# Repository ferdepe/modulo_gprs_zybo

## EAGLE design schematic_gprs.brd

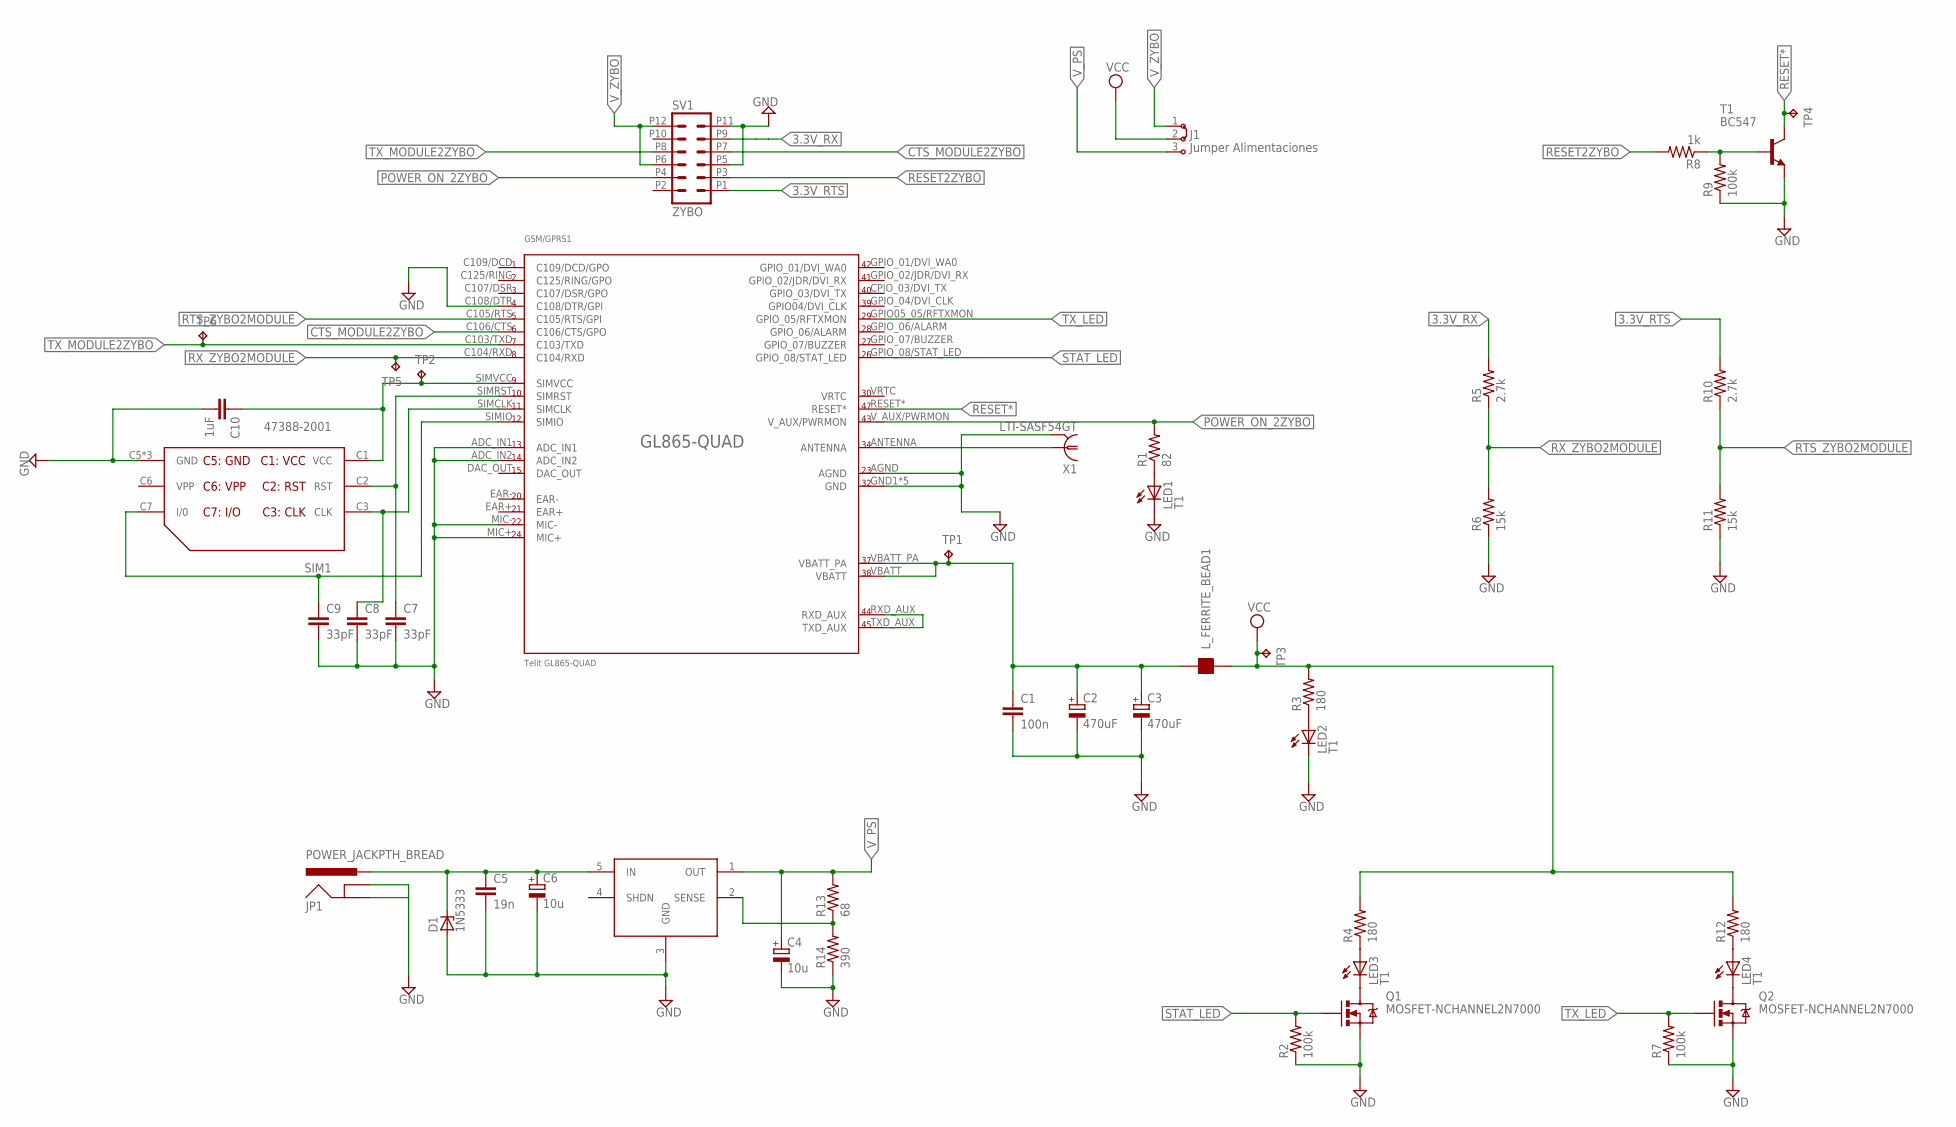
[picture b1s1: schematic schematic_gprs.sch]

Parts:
C1: 100n; C2.5-2
C2, C3: 470uF; E3,5-8
C4: 10u; E2-5
C5: 19n; C050-025X075
C6: 10u; E1,8-4
C7, C8, C9: 33pF; C025-024X044
C10: 1uF; CAP-PTH-SMALL-KIT
D1: 1N5333; C1702-15
GSM/GPRS1: Telit GL865-QUAD; GL865-QUAD
J1: Jumper Alimentaciones; 04C
JP1: POWER_JACKPTH_BREAD; POWER_JACK_PTH_BREAD
LED1, LED2, LED3, LED4: T1; LED3MM
L_FERRITE_BEAD1: FERRITEBEAD2; 0207/7
Q1, Q2: MOSFET-NCHANNEL2N7000; TO-92
R1: 82; 0207/7
R2, R7, R9: 100k; 0207/7
R3, R4, R12: 180; 0207/7
R5, R10: 2.7k; 0207/7
R6, R11: 15k; 0207/7
R8: 1k; 0207/7
R13: 68; 0207/7
R14: 390; 0207/7
SIM1: 47388-2001
SV1: ZYBO; MA06-2
T1: BC547; TO92
TP1, TP2, TP3, TP4, TP5, TP6: TPPAD1-13; P1-13
U$1: LT1528; Q5-DD
X1: LTI-SASF54GT

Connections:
3.3V_RTS: R10.2, SV1.P1 (1)
3.3V_RX: R5.2, SV1.P9 (9)
CTS_MODULE2ZYBO: GSM/GPRS1.C106/CTS (C106/CTS/GPO), SV1.P7 (7)
GND: C1.2, C2.-, C3.-, C4.-, C5.2, C6.-, C7.2, C8.2, C9.2, C10.2, D1.A, GSM/GPRS1.ADC_IN1, GSM/GPRS1.ADC_IN2, GSM/GPRS1.AGND, GSM/GPRS1.C108/DTR (C108/DTR/GPI), GSM/GPRS1.GND1 (GND), GSM/GPRS1.GND2 (GND), GSM/GPRS1.GND3 (GND), GSM/GPRS1.GND4 (GND), GSM/GPRS1.GND5 (GND), GSM/GPRS1.MIC+, GSM/GPRS1.MIC-, JP1.GND, JP1.GNDBREAK, LED1.K (C), LED2.K (C), Q1.1 (S), Q2.1 (S), R2.1, R6.1, R7.1, R9.1, R11.1, R14.1, SIM1.C5 (GND), SIM1.GND1 (GND), SIM1.GND2 (GND), SV1.P5 (5), SV1.P11 (11), T1.1 (E), U$1.3 (GND), X1.2, X1.3 (2), X1.4 (2), X1.5 (2)
unnamed: GSM/GPRS1.ANTENNA, X1.1
unnamed: C10.1, GSM/GPRS1.SIMVCC, SIM1.C1 (VCC), TP2.TP
unnamed: LED4.A, R12.1
unnamed: C7.1, GSM/GPRS1.SIMRST, SIM1.C2 (RST)
unnamed: C8.1, GSM/GPRS1.SIMCLK, SIM1.C3 (CLK)
unnamed: C9.1, GSM/GPRS1.SIMIO, SIM1.C7 (I/0)
unnamed: R8.1, R9.2, T1.2 (B)
unnamed: LED1.A, R1.1
unnamed: LED4.K (C), Q2.3 (D)
unnamed: C1.1, C2.+, C3.+, GSM/GPRS1.VBATT, GSM/GPRS1.VBATT_PA, L_FERRITE_BEAD1.1 (A), TP1.TP
unnamed: C5.1, C6.+, D1.C, JP1.PWR, U$1.5 (IN)
unnamed: LED3.A, R4.1
unnamed: LED3.K (C), Q1.3 (D)
unnamed: R13.1, R14.2, U$1.2 (SENSE)
unnamed: LED2.A, R3.1
unnamed: GSM/GPRS1.RXD_AUX, GSM/GPRS1.TXD_AUX
POWER_ON_2ZYBO: GSM/GPRS1.V_AUX/PWRMON, R1.2, SV1.P4 (4)
RESET2ZYBO: R8.2, SV1.P3 (3)
RESET*: GSM/GPRS1.RESET*, T1.3 (C), TP4.TP
RTS_ZYBO2MODULE: GSM/GPRS1.C105/RTS (C105/RTS/GPI), R10.1, R11.2
RX_ZYBO2MODULE: GSM/GPRS1.C104/RXD, R5.1, R6.2, TP5.TP
STAT_LED: GSM/GPRS1.GPIO_08/STAT_LED, Q1.2 (G), R2.2
TX_LED: GSM/GPRS1.GPIO05_05/RFTXMON (GPIO_05/RFTXMON), Q2.2 (G), R7.2
TX_MODULE2ZYBO: GSM/GPRS1.C103/TXD, SV1.P8 (8), TP6.TP
VCC: J1.2, L_FERRITE_BEAD1.2 (B), R3.2, R4.2, R12.2, TP3.TP
V_PS: C4.+, J1.3, R13.2, U$1.1 (OUT)
V_ZYBO: J1.1, SV1.P6 (6), SV1.P12 (12)

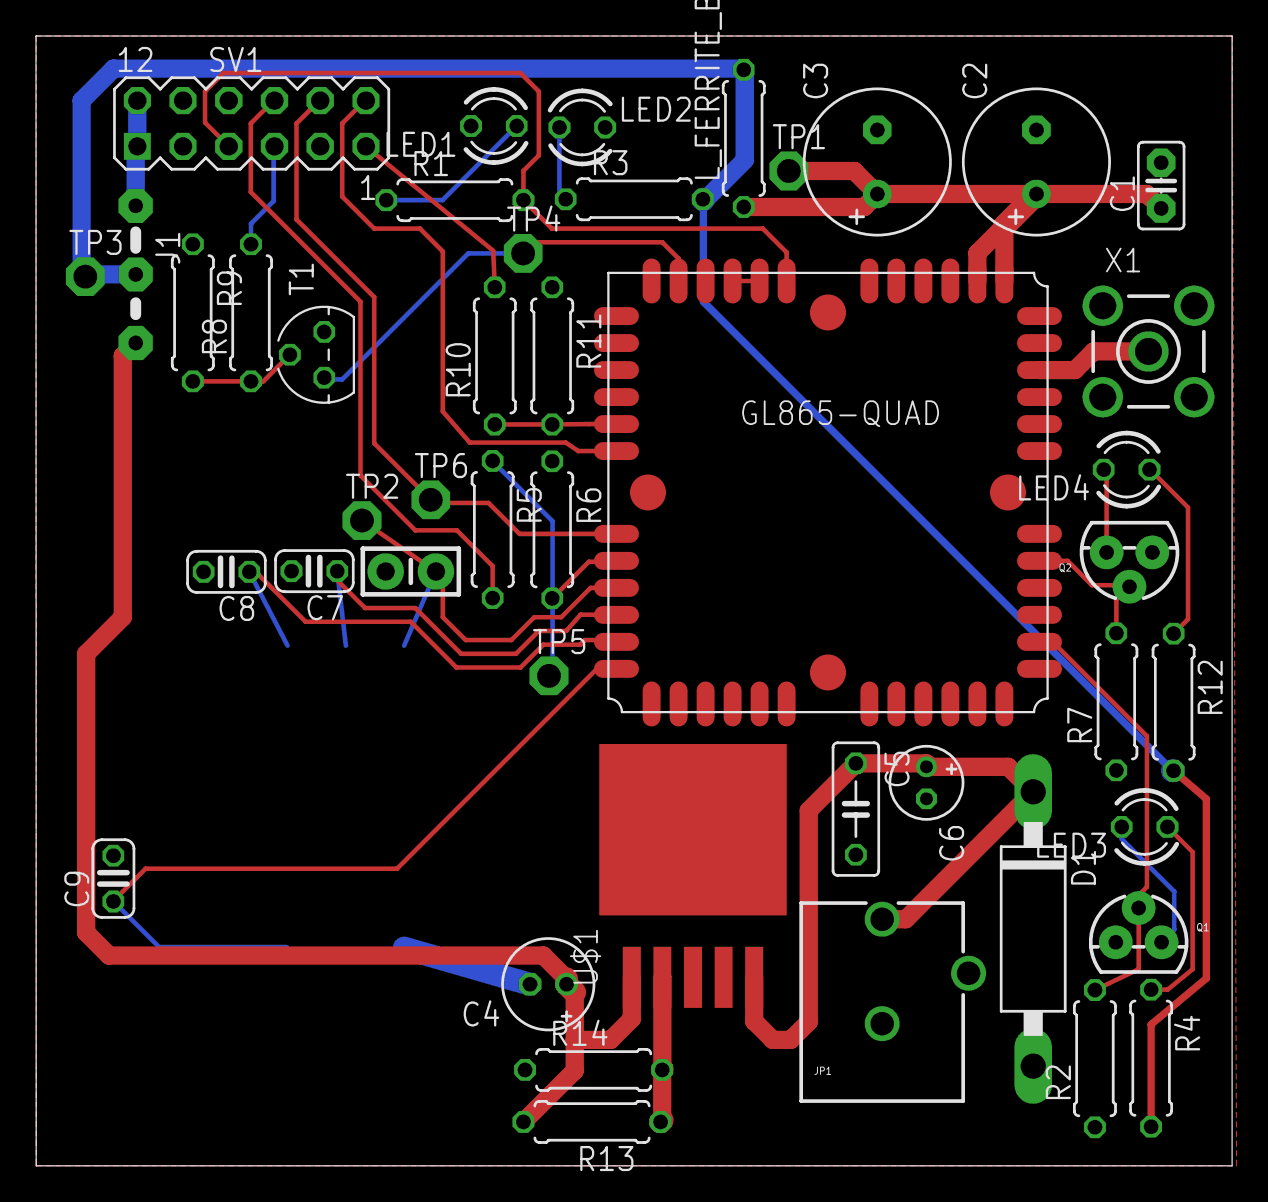
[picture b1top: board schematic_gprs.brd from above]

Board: 2 copper layers, 66.5 x 62.8 mm, 46 parts (1 on the bottom side), 31 nets.

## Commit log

2016-02-09 :lollipop: Added .gitattributes & .gitignore files
2016-02-09 Cambios varios
    Se cambian valores de las resistencias de LED, se añade condensador
    cerámico bypass de 1uF a la alimentación de SIM.
2016-02-09 Pistas realizadas
    Se acaban todas las conexiones restantes. Se replantean los valores de
    las resistencias para el led y se modifican también los valores de las
    resistencias a la salida del regulador de tensión. Se añade un
    condensador de 1uF a la entrada de VCC de la tarjeta SIM:
2016-02-11 Resultado Final
    PCB a espera de revisión por tutor el día 18/02/2015

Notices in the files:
parts and their libraries:
SparkFun-DiscreteSemi: Licensing: Creative Commons ShareAlike 4.0 International - https://creativecommons.org/licenses/by-sa/4.0
